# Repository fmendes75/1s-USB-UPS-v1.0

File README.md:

# 1s USB UPS v1.0
## Objective
The name of the project means One Second USB UPS.
The obective is to create a low cost and simple USB plugin with Super Capacitors that can power a SBC like Raspberry Pi during a few seconds, giving time for a proper shutdown.

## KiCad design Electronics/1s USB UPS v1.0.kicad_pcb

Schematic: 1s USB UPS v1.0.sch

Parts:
C1, C2: C; C_0805_2012Metric_Pad1.15x1.40mm_HandSolder
C3: 10uF; CP_EIA-2012-15_AVX-P_Pad1.30x1.05mm_HandSolder
C4, C5, C9: 0.1uF; C_0402_1005Metric
C6: CAP; CP_Axial_L11.0mm_D5.0mm_P18.00mm_Horizontal
C7, C8: 1uF; C_0603_1608Metric_Pad1.05x0.95mm_HandSolder
D1: D_TVS_ALT; D_SMB
F1: Polyfuse; C_1206_3216Metric_Pad1.42x1.75mm_HandSolder
J1: Conn_01x02; PinHeader_2x01_P2.54mm_Vertical
J2: USB_B_Micro; USB_Micro-B_Wuerth_629105150521
J3: Conn_02x03_Odd_Even; PinHeader_2x03_P2.54mm_Vertical
J4: USB_A; USB_A_CNCTech_1001-011-01101_Horizontal
R1: R; R_0603_1608Metric_Pad1.05x0.95mm_HandSolder
R2: 1M; R_0603_1608Metric_Pad1.05x0.95mm_HandSolder
R3, R4: 22R; R_0603_1608Metric_Pad1.05x0.95mm_HandSolder
U1: ATmega16U4-MU; QFN-44-1EP_7x7mm_P0.5mm_EP5.4x5.4mm
Y1: 16MHz; Crystal_SMD_HC49-SD_HandSoldering

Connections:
/*Reset: C4.1, J1.2, R1.2, U1.13
/D+: R3.1, U1.4
/D-: R4.1, U1.3; also elsewhere on the board
/MISO: J3.1, U1.11
/MOSI: J3.4, U1.10
/Reset: J3.5
/SCK: J3.3, U1.9
/XTAL1: C1.1, R2.1, U1.17, Y1.1
/XTAL2: C2.1, R2.2, U1.16, Y1.2
GND: C1.2, C2.2, C3.2, C4.2, C5.2, C6.2, C7.2, C8.2, C9.2, D1.2, J1.1, J2.5, J2.6, J3.6, J4.4, J4.5, U1.5, U1.15, U1.23, U1.35, U1.43, U1.45; also elsewhere on the board
unnamed: C7.1, U1.6
unnamed: F1.2, J2.1
unnamed 16: J4.2, R4.2; also elsewhere on the board
unnamed: J4.3, R3.2
VCC: C3.1, C5.1, C6.1, C8.1, C9.1, D1.1, F1.1, J3.2, J4.1, R1.1, U1.2, U1.7, U1.14, U1.24, U1.34, U1.44; also elsewhere on the board

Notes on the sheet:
ICSP - Programming

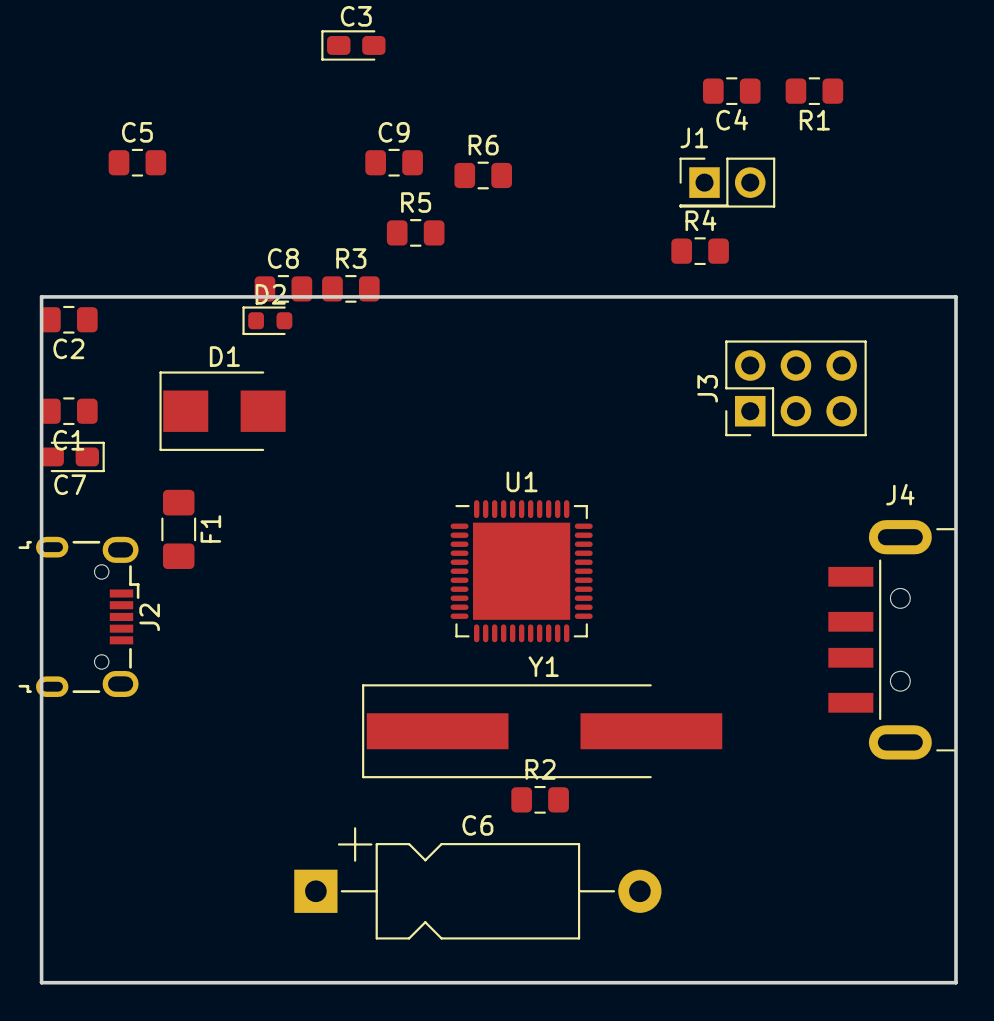
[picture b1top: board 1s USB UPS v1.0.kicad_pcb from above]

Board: 2 copper layers, 50.8 x 38.1 mm, 24 parts (0 on the bottom side), 14 nets, no tracks yet.

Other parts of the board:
D2: D_Zener_ALT; D_0603_1608Metric
R5: 22R; R_0805_2012Metric_Pad1.15x1.40mm_HandSolder
R6: R; R_0805_2012Metric_Pad1.15x1.40mm_HandSolder

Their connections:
/D-: R5.1; also elsewhere on the board
GND: R6.2; also elsewhere on the board
unnamed 16: R5.2; also elsewhere on the board
VCC: D2.1, R6.1; also elsewhere on the board

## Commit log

2018-09-23 Creation
2018-11-12 Folder re-org
2018-11-12 Create README.md file
2018-11-13 [Add] Arduino and RaspberryPi code
    Adds Arduino tester code and its Readme File
    Adds RaspberryPi python script and its Readme File
2018-11-20 Rollback readme.md
